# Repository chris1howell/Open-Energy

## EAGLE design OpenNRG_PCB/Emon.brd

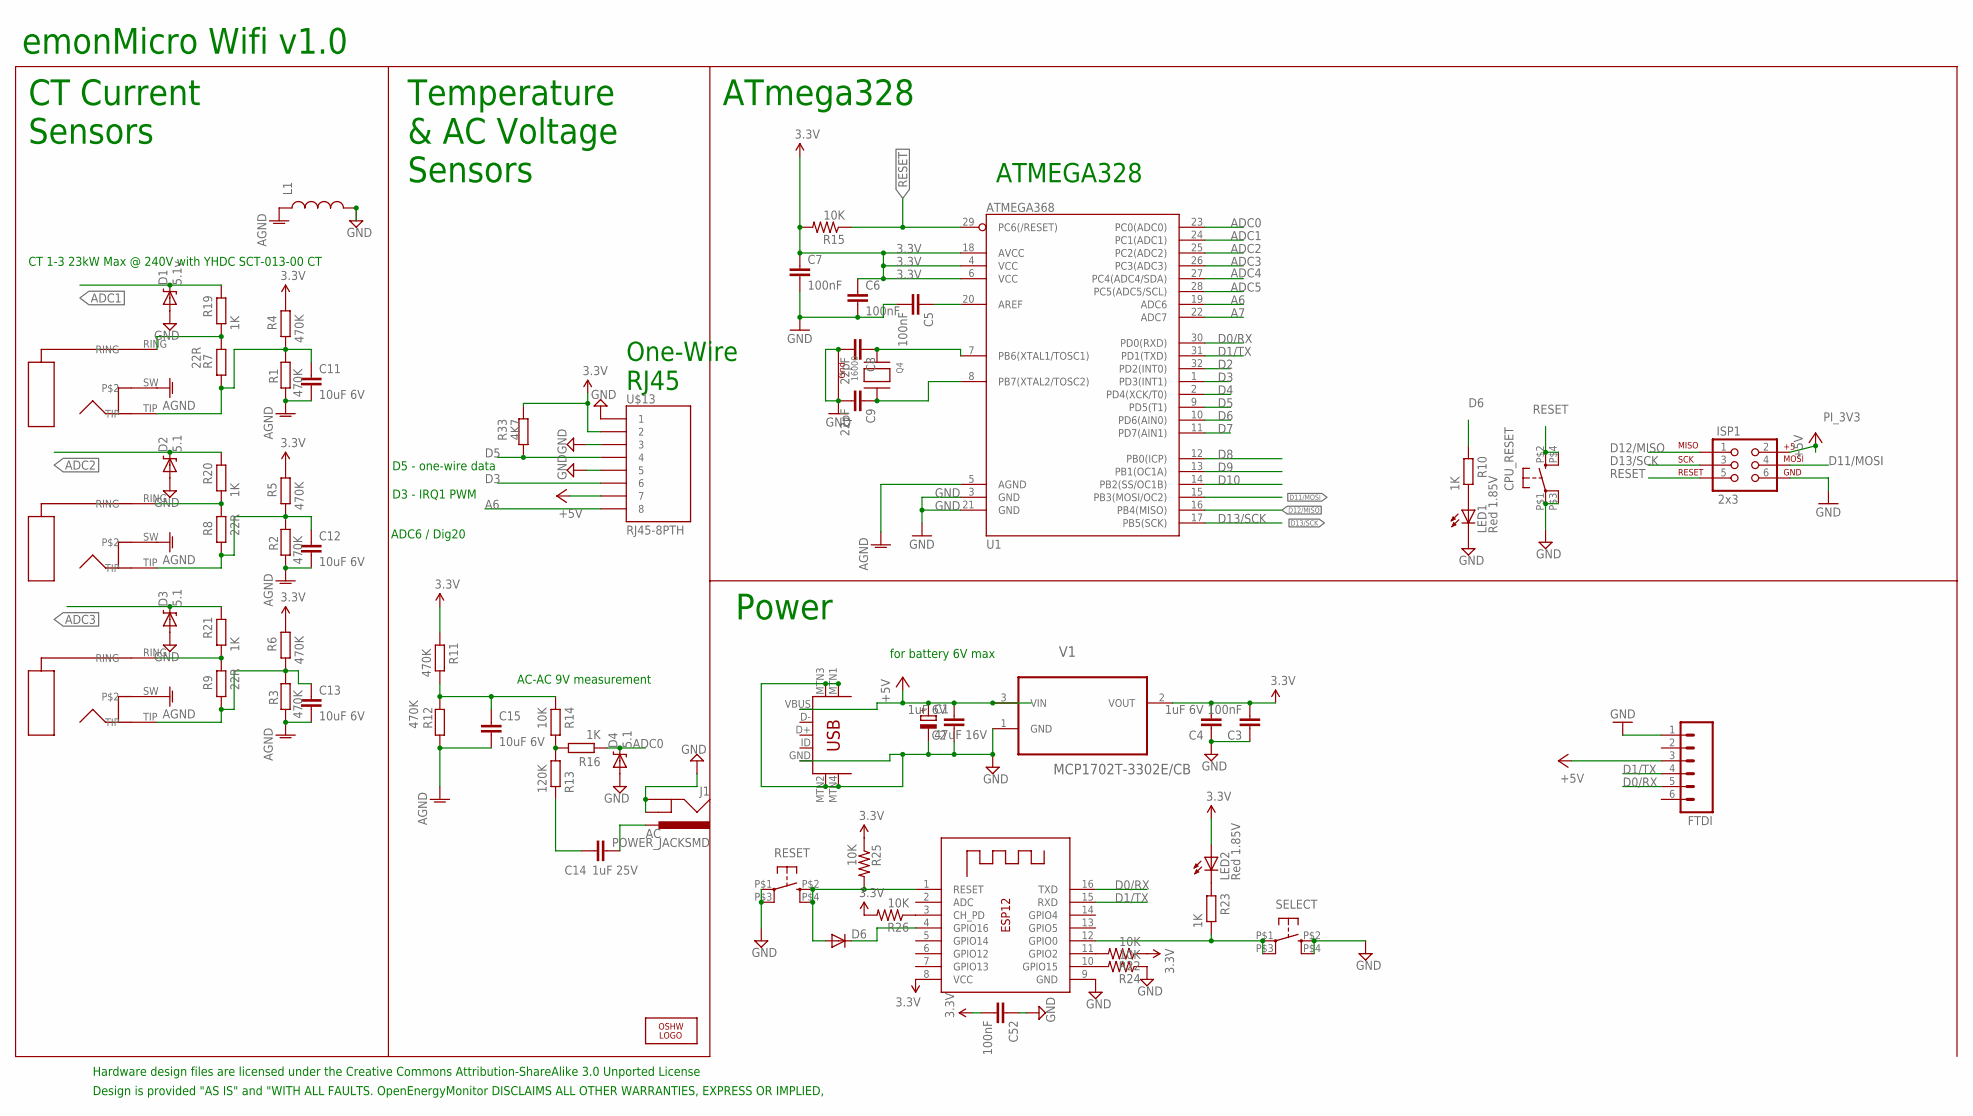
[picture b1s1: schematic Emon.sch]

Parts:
C1: 47uF 16V; PANASONIC_D
C2, C4: 1uF 6V; C0603
C3, C5, C6, C7, C52: 100nF; C0603
C8, C9: 22pF; C0603
C11, C12, C13, C15: 10uF 6V; C0603
C14: 1uF 25V; C0603
CPU_RESET: KMR211GLFS; PUSHBUTTON-KMR241GLFS
D1: 5.1v; SOD-323
D2, D3, D4: 5.1; SOD-323
D6: DIODESOD; SOD-323
FTDI: M06LOCK; 1X06_LOCK
ISP1: 2x3; 2X3
J1: POWER_JACKSMD; POWER_JACK_SMD
L1: INDUCTOR0603; 0603
LED1, LED2: Red 1.85V; CHIP-LED0805
LOGO1: OSHW_LOGO_6MILX0200-NT; OSHW_6X200_NOTEXT
Q4: 16000; NX3225
R1, R2, R3, R4, R5, R6, R11, R12: 470K; R0603
R7, R8, R9: 22R; R1206
R10, R16, R19, R20, R21, R23: 1K; R0603
R13: 120K; R0603
R14, R15, R22, R24, R25, R26: 10K; R0603
R33: 4K7; R0603
RESET: KMR211GLFS; PUSHBUTTON-KMR241GLFS
SELECT: KMR211GLFS; PUSHBUTTON-KMR241GLFS
U1: ATMEGA368; TQFP32-08
U$1, U$2, U$3: MJ-3523-SMT; AUDIO_SMT
U$13: RJ45-8PTH; RJ45-8
USB_POWER: USB-MINIB-5PIN; USB-MINIB-CISECO
V1: MCP1702T-3302E/CB; SOT95P237X112-3N
X1: ESP-12

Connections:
3.3V: C3.2, C4.2, C6.1, C7.1, C52.2, LED2.A, R4.2, R5.2, R6.2, R11.2, R15.2, R22.1, R25.1, R26.2, R33.1, U1.4 (VCC), U1.6 (VCC), U1.18 (AVCC), U$13.2, V1.2 (VOUT), X1.8 (VCC)
+5V: C1.+, C2.2, FTDI.3, ISP1.2, U$13.7, USB_POWER.VBUS, V1.3 (VIN)
A6: U1.19 (ADC6), U$13.8
A7: U1.22 (ADC7)
AC: C14.2, J1.VIN0 (PWR)
ADC0: D4.1 (C), R16.1, U1.23 (PC0(ADC0))
ADC1: D1.1 (C), R19.2, U1.24 (PC1(ADC1))
ADC2: D2.1 (C), R20.2, U1.25 (PC2(ADC2))
ADC3: D3.1 (C), R21.2, U1.26 (PC3(ADC3))
ADC4: U1.27 (PC4(ADC4/SDA))
ADC5: U1.28 (PC5(ADC5/SCL))
AGND: C11.2, C12.2, C13.2, C15.2, L1.1, R1.2, R2.2, R3.2, R12.1, U1.5 (AGND), U$1.SW, U$2.SW, U$3.SW
D0/RX: FTDI.5, U1.30 (PD0(RXD)), X1.16 (TXD)
D1/TX: FTDI.4, U1.31 (PD1(TXD)), X1.15 (RXD)
D2: U1.32 (PD2(INT0))
D3: U1.1 (PD3(INT1)), U$13.6
D4: U1.2 (PD4(XCK/T0))
D5: R33.2, U1.9 (PD5(T1)), U$13.4
D6: R10.2, U1.10 (PD6(AIN0))
D7: U1.11 (PD7(AIN1))
D8: U1.12 (PB0(ICP))
D9: U1.13 (PB1(OC1A))
D10: U1.14 (PB2(SS/OC1B))
D11/MOSI: ISP1.4, U1.15 (PB3(MOSI/OC2))
D12/MISO: ISP1.1, U1.16 (PB4(MISO))
D13/SCK: ISP1.3, U1.17 (PB5(SCK))
GND: C1.-, C2.1, C3.1, C4.1, C5.2, C6.2, C7.2, C8.2, C9.2, C52.1, CPU_RESET.P$1 (1), CPU_RESET.P$3 (3), D1.2 (A), D2.2 (A), D3.2 (A), D4.2 (A), FTDI.1, ISP1.6, J1.GND (GNDBREAK), J1.P$4 (GND), L1.2, LED1.C, Q4.1 (G1), Q4.3 (G2), R24.1, RESET.P$1 (1), RESET.P$3 (3), SELECT.P$2 (2), SELECT.P$4 (4), U1.3 (GND), U1.21 (GND), U$13.1, U$13.3, U$13.5, USB_POWER.GND, USB_POWER.MTN1 (MTN2), USB_POWER.MTN2 (MTN3), USB_POWER.MTN3 (MTN1), USB_POWER.MTN4, V1.1 (GND), X1.9 (GND)
GND1: R23.1, SELECT.P$1 (1), SELECT.P$3 (3), X1.12 (GPIO0)
unnamed: C8.1, Q4.2 (X1), U1.7 (PB6(XTAL1/TOSC1))
unnamed: R7.2, R19.1, U$2.RING
unnamed: C13.1, R3.1, R6.1, R9.1, U$3.TIP
unnamed: R13.2, R14.1, R16.2
unnamed: R24.2, X1.10 (GPIO15)
unnamed: R22.2, X1.11 (GPIO2)
unnamed: C14.1, R13.1
unnamed: R26.1, X1.3 (CH_PD)
unnamed: R8.2, R20.1, U$1.RING
unnamed: LED2.C, R23.2
unnamed: D6.1 (C), X1.4 (GPIO16)
unnamed: R9.2, R21.1, U$3.RING
unnamed: C9.1, Q4.4 (X2), U1.8 (PB7(XTAL2/TOSC2))
unnamed: D6.2 (A), R25.2, RESET.P$2 (2), RESET.P$4 (4), X1.1 (RESET)
unnamed: C5.1, U1.20 (AREF)
unnamed: C12.1, R2.1, R5.1, R8.1, U$1.TIP
unnamed: C15.1, R11.1, R12.2, R14.2
unnamed: C11.1, R1.1, R4.1, R7.1, U$2.TIP
unnamed: LED1.A, R10.1
RESET: CPU_RESET.P$2 (2), CPU_RESET.P$4 (4), ISP1.5, R15.1, U1.29 (PC6(/RESET))

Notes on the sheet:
AC-AC 9V measurement
CT 1-3 23kW Max @ 240V with YHDC SCT-013-00 CT
for battery 6V max
Power
ATmega328
CT Current Sensors
Temperature & AC Voltage Sensors
Design is provided "AS IS" and "WITH ALL FAULTS. OpenEnergyMonitor DISCLAIMS ALL OTHER WARRANTIES, EXPRESS OR IMPLIED,
Hardware design files are licensed under the Creative Commons Attribution-ShareAlike 3.0 Unported License
emonMicro Wifi v1.0
ATMEGA328
One-Wire RJ45
D3 - IRQ1 PWM
D5 - one-wire data
ADC6 / Dig20

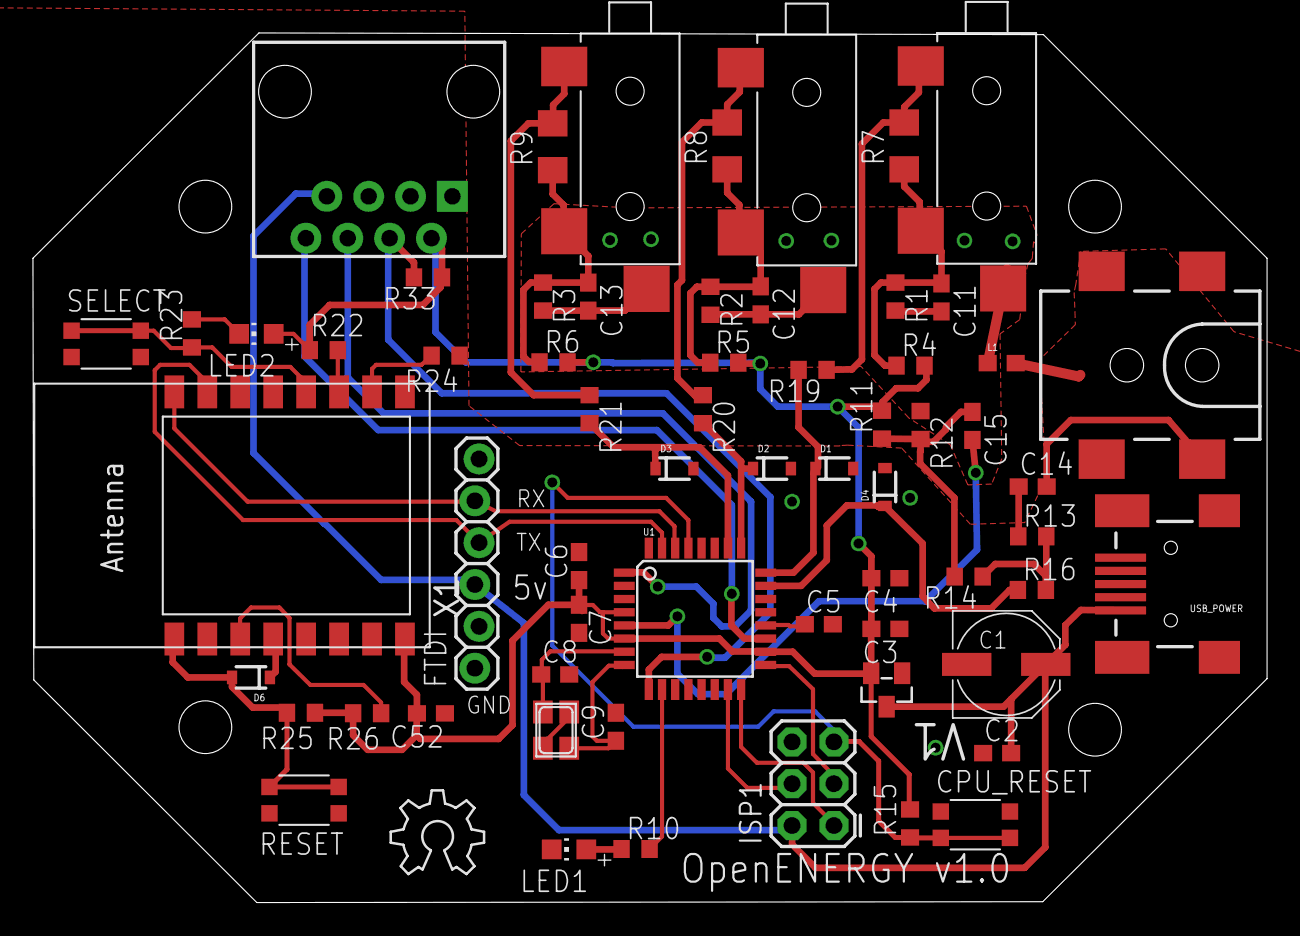
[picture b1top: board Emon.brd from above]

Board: 2 copper layers, 74.9 x 52.8 mm, 64 parts (0 on the bottom side), 39 nets.

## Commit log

2015-08-23 :octocat: Added .gitattributes & .gitignore files
2015-08-23 Open Energy
    Initial release
2015-08-23 OpenNRG Hardware
    Initial release
2015-11-25 Re-write or ESP code and updated to board files
    Update to ESP8266 firmware to support latest board manager.

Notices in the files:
parts and their libraries:
SparkFun-Connectors: Licensing: CC v3.0 Share-Alike You are welcome to use this library for commercial purposes.
